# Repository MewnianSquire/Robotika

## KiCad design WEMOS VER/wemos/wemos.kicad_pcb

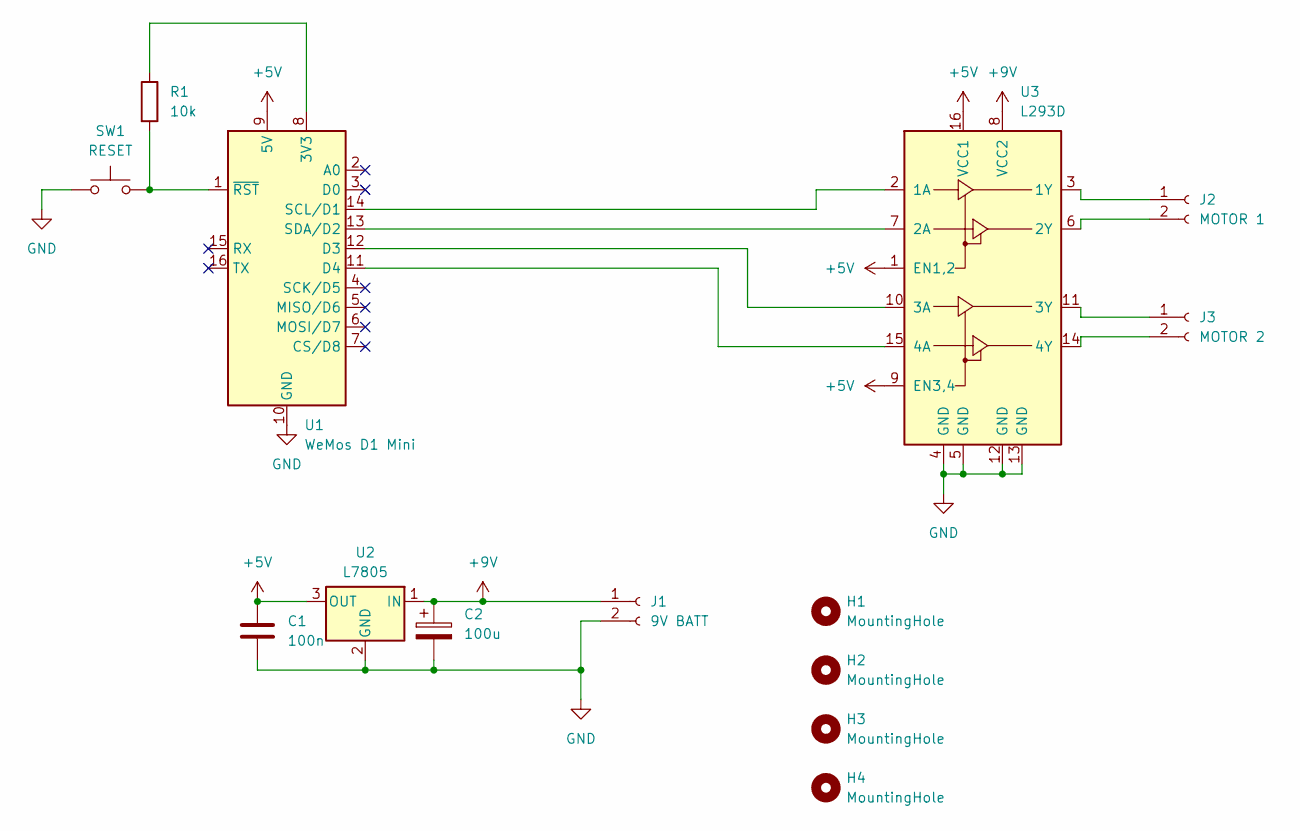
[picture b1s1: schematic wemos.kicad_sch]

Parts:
C1: 100n; C_Disc_D5.0mm_W2.5mm_P5.00mm
C2: 100u; CP_Radial_D5.0mm_P2.50mm
H1, H2, H3, H4: MountingHole; MountingHole_3.2mm_M3
J1: 9V BATT; PinHeader_1x02_P2.54mm_Vertical
J2: MOTOR 1; PinHeader_1x02_P2.54mm_Vertical
J3: MOTOR 2; PinHeader_1x02_P2.54mm_Vertical
R1: 10k; R_Axial_DIN0207_L6.3mm_D2.5mm_P7.62mm_Horizontal
SW1: RESET; SW_PUSH_6mm
U1: WeMos D1 Mini; WEMOS_D1_mini_light
U2: L7805; TO-220-3_Vertical
U3: L293D; DIP-16_W7.62mm

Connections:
+5V: C1.1, U1.9 (5V), U2.3 (OUT), U3.1 (EN1,2), U3.9 (EN3,4), U3.16 (VCC1)
+9V: C2.1, J1.1, U2.1 (IN), U3.8 (VCC2)
GND: C1.2, C2.2, J1.2, SW1.1, U1.10 (GND), U2.2 (GND), U3.4 (GND), U3.5 (GND), U3.12 (GND), U3.13 (GND)
unnamed: J2.1, U3.3 (1Y)
unnamed: J2.2, U3.6 (2Y)
unnamed: J3.1, U3.11 (3Y)
unnamed: J3.2, U3.14 (4Y)
unnamed: R1.1, U1.8 (3V3)
unnamed: U1.12 (D3), U3.10 (3A)
unnamed: U1.11 (D4), U3.15 (4A)
unnamed: U1.14 (SCL/D1), U3.2 (1A)
unnamed: U1.13 (SDA/D2), U3.7 (2A)
unnamed: R1.2, SW1.2, U1.1 (~RST)

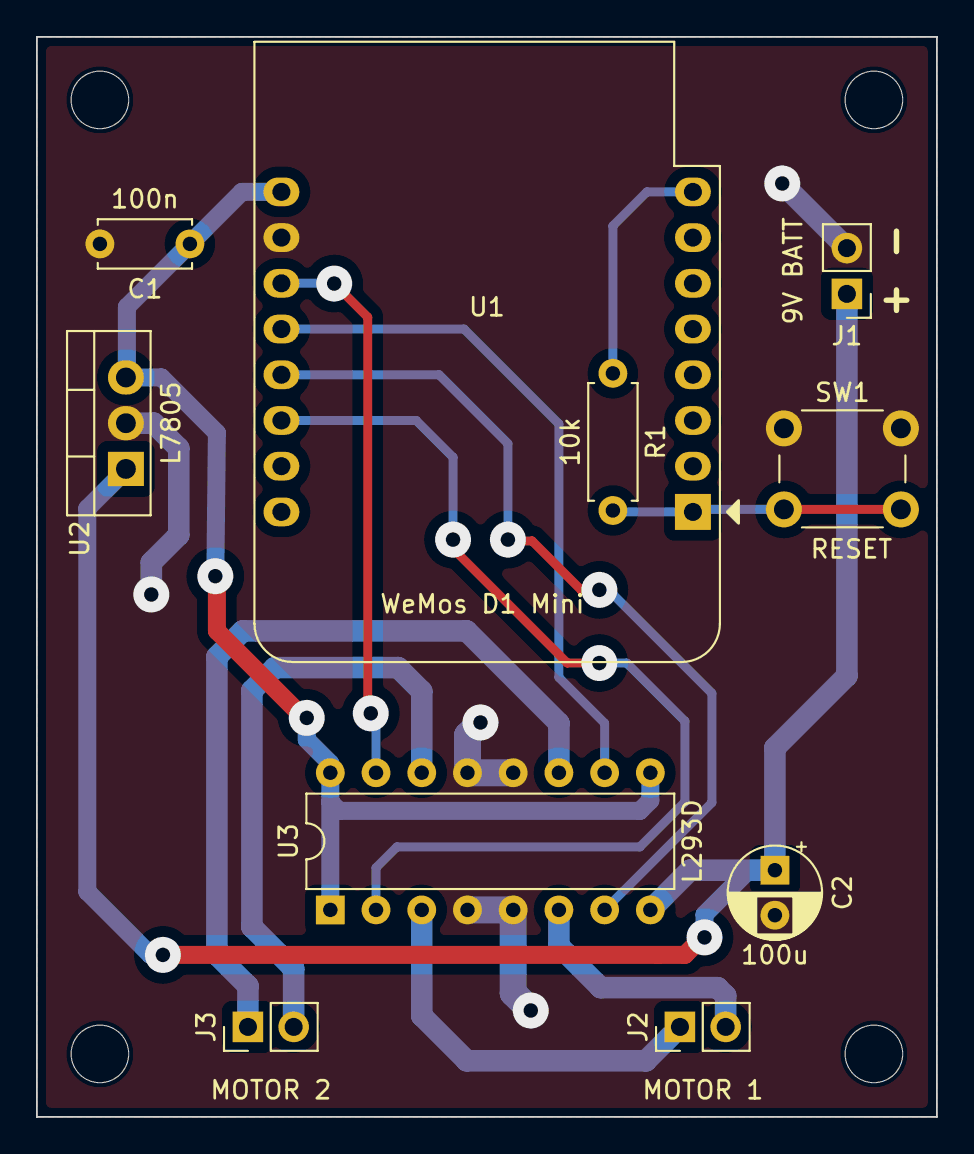
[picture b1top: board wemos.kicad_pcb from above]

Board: 2 copper layers, 50.0 x 60.0 mm, 14 parts (0 on the bottom side), 13 nets.

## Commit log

2024-04-27 esp32 test code
    bisa dipake di esp32 full udah dicoba pake motor juga aman bisa AP atau Web Server tergantung mode
2024-04-28 work
    pcb pdf revision
2024-04-29 work
2024-04-30 adjustments
2024-05-03 revisions
2024-05-07 woek
